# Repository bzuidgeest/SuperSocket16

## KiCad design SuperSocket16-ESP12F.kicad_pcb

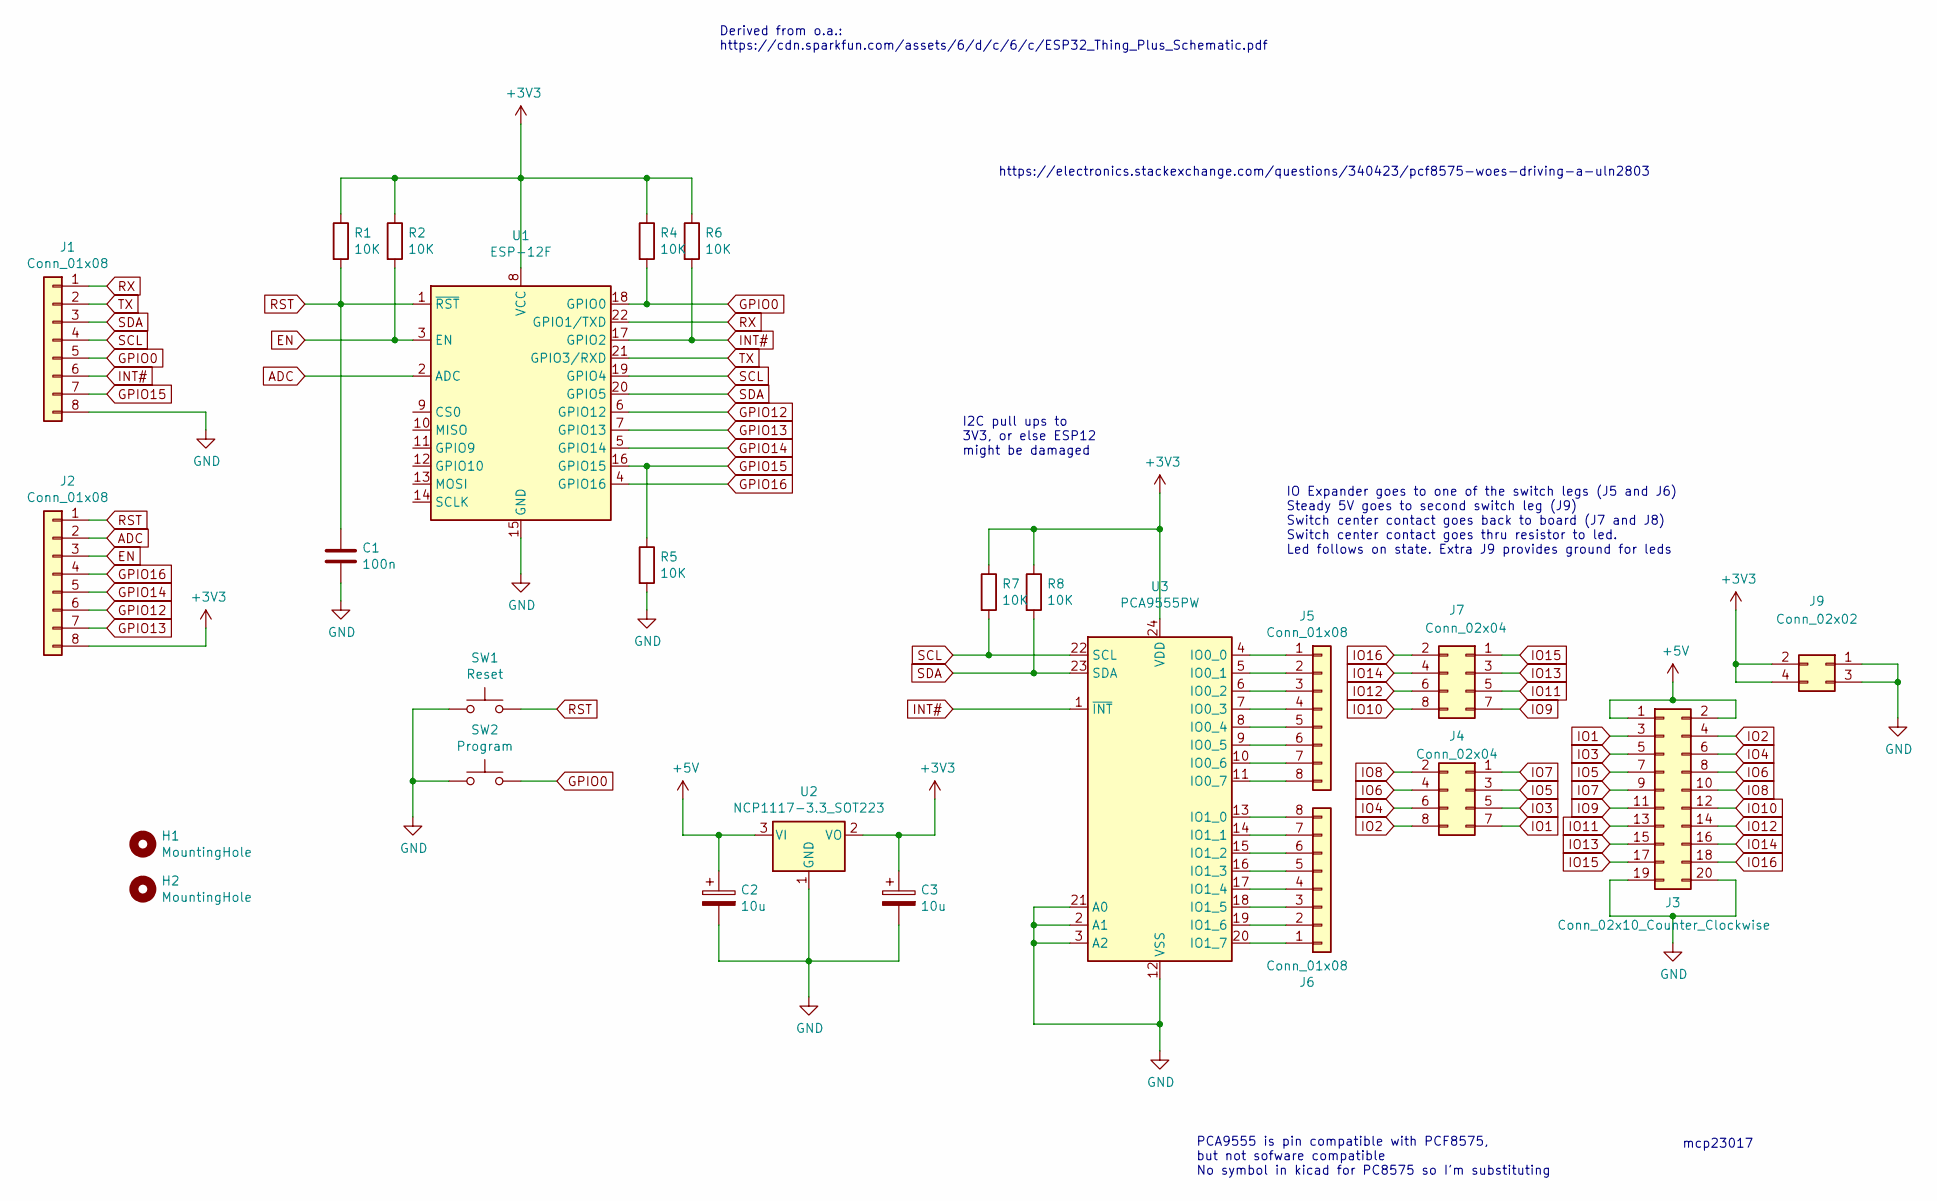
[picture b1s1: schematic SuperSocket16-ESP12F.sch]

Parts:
C1: 100n; C_Axial_L5.1mm_D3.1mm_P7.50mm_Horizontal
C2, C3: 10u; C_Radial_D5.0mm_H7.0mm_P2.00mm
H1, H2: MountingHole; MountingHole_3.2mm_M3_DIN965
J1, J2, J5, J6: Conn_01x08; PinHeader_1x08_P2.54mm_Vertical
J3: Conn_02x10_Counter_Clockwise; PinHeader_2x10_P2.54mm_Vertical
J4, J7: Conn_02x04; PinHeader_2x04_P2.54mm_Vertical
J9: Conn_02x02; PinHeader_2x02_P2.54mm_Vertical
R1, R2, R4, R5, R6, R7, R8: 10K; R_Axial_DIN0207_L6.3mm_D2.5mm_P7.62mm_Horizontal
SW1: Reset; SW_PUSH_6mm
SW2: Program; SW_PUSH_6mm
U1: ESP-12F; ESP-12E
U2: NCP1117-3.3_SOT223; SOT-223-3_TabPin2
U3: PCA9555PW; TSSOP-24_4.4x7.8mm_P0.65mm

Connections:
+3V3: C3.1, J2.8, J9.2, J9.4, R1.1, R2.1, R4.1, R6.1, R7.1, R8.1, U1.8 (VCC), U2.2 (VO), U3.24 (VDD)
+5V: C2.1, J3.1, J3.2, U2.3 (VI)
ADC: J2.2, U1.2 (ADC)
EN: J2.3, R2.2, U1.3 (EN)
GND: C1.2, C2.2, C3.2, J1.8, J3.19, J3.20, J9.1, J9.3, R5.2, SW1.1, SW2.1, U1.15 (GND), U2.1 (GND), U3.2 (A1), U3.3 (A2), U3.12 (VSS), U3.21 (A0)
GPIO0: J1.5, R4.2, SW2.2, U1.18 (GPIO0)
GPIO12: J2.6, U1.6 (GPIO12)
GPIO13: J2.7, U1.7 (GPIO13)
GPIO14: J2.5, U1.5 (GPIO14)
GPIO15: J1.7, R5.1, U1.16 (GPIO15)
GPIO16: J2.4, U1.4 (GPIO16)
INT#: J1.6, R6.2, U1.17 (GPIO2), U3.1 (~INT)
IO1: J3.3, J4.7
IO2: J3.4, J4.8
IO3: J3.5, J4.5
IO4: J3.6, J4.6
IO5: J3.7, J4.3
IO6: J3.8, J4.4
IO7: J3.9, J4.1
IO8: J3.10, J4.2
IO9: J3.11, J7.7
IO10: J3.12, J7.8
IO11: J3.13, J7.5
IO12: J3.14, J7.6
IO13: J3.15, J7.3
IO14: J3.16, J7.4
IO15: J3.17, J7.1
IO16: J3.18, J7.2
unnamed: J5.1, U3.4 (IO0_0)
unnamed: J5.2, U3.5 (IO0_1)
unnamed: J5.3, U3.6 (IO0_2)
unnamed: J5.4, U3.7 (IO0_3)
unnamed: J5.5, U3.8 (IO0_4)
unnamed: J5.6, U3.9 (IO0_5)
unnamed: J5.7, U3.10 (IO0_6)
unnamed: J5.8, U3.11 (IO0_7)
unnamed: J6.1, U3.20 (IO1_7)
unnamed: J6.2, U3.19 (IO1_6)
unnamed: J6.3, U3.18 (IO1_5)
unnamed: J6.4, U3.17 (IO1_4)
unnamed: J6.5, U3.16 (IO1_3)
unnamed: J6.6, U3.15 (IO1_2)
unnamed: J6.7, U3.14 (IO1_1)
unnamed: J6.8, U3.13 (IO1_0)
RST: C1.1, J2.1, R1.2, SW1.2, U1.1 (~RST)
RX: J1.1, U1.22 (GPIO1/TXD)
SCL: J1.4, R7.2, U1.19 (GPIO4), U3.22 (SCL)
SDA: J1.3, R8.2, U1.20 (GPIO5), U3.23 (SDA)
TX: J1.2, U1.21 (GPIO3/RXD)

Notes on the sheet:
PCA9555 is pin compatible with PCF8575, but not sofware compatible No symbol in kicad for PC8575 so I'm substituting
Derived from o.a.: https://cdn.sparkfun.com/assets/6/d/c/6/c/ESP32_Thing_Plus_Schematic.pdf
IO Expander goes to one of the switch legs (J5 and J6) Steady 5V goes to second switch leg (J9) Switch center contact goes back to board (J7 and J8) Switch center contact goes thru resistor to led. Led follows on state. Extra J9 provides ground for leds
I2C pull ups to 3V3, or else ESP12 might be damaged
mcp23017
https://electronics.stackexchange.com/questions/340423/pcf8575-woes-driving-a-uln2803

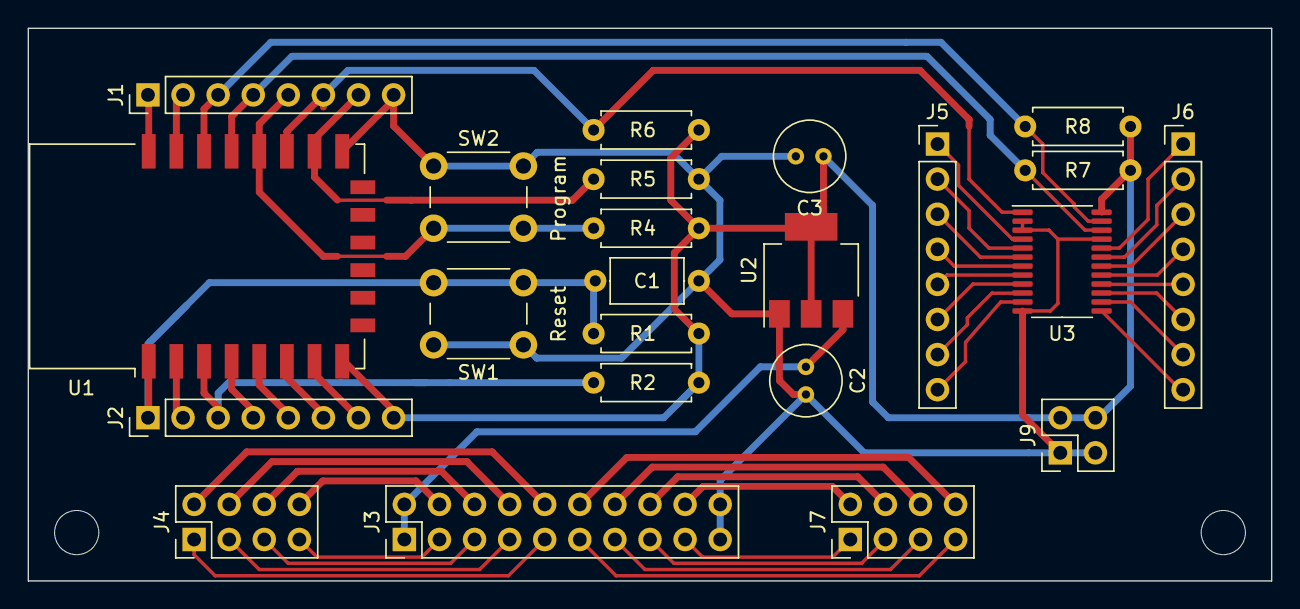
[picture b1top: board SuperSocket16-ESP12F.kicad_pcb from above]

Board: 2 copper layers, 90.0 x 40.0 mm, 25 parts (0 on the bottom side), 49 nets.

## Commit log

2021-04-25 Init repo
2021-04-28 Should be fully wired now. Fixed some mistakes pertaining to voltages.
